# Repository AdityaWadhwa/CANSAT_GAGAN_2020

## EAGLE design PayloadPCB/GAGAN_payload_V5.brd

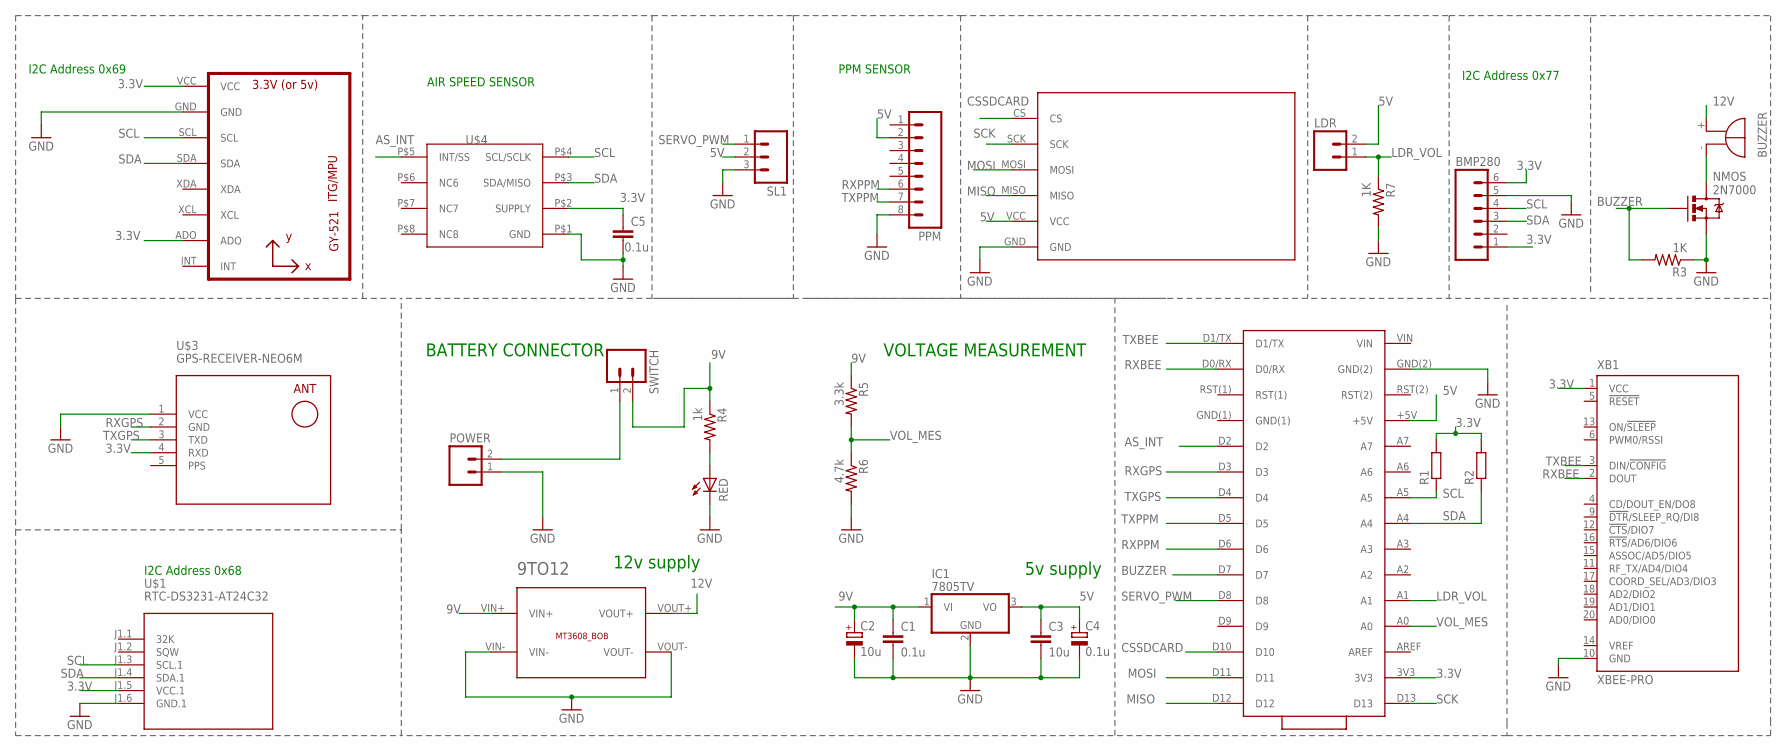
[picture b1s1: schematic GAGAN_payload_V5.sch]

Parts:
9TO12: BREAKOUTS_MT3608_BOB
BMP280: M06; 06P
C1, C5: 0.1u; C025-025X050
C2: 10u; E2,5-6
C3: 10u; C025-025X050
C4: 0.1u; E2,5-6
IC1: 7805TV; TO220V
LDR: M02; 02P
MOD1: ARDUINO(NANO_3.0); ARDUINO_NANO_30PIN
POWER: CEDT_JANUARY_2015_V5_M02; CEDT_JANUARY_2015_V5_02P
PPM: M08; 08P
Q1: SPARKFUN-DISCRETESEMI_MOSFET-NCHANNEL2N7000; SPARKFUN-DISCRETESEMI_TO-92
R1, R2: R-EU_0207/7; 0207/7
R3, R7: 1K; 0204/7
R4: 1k; 0204/7
R5: 3.3k; 0204/7
R6: 4.7k; 0204/7
RED: red; LED3MM
SG1: BUZZER_EB2209A
SL1: M03; 03P
SWITCH: M02; 02P
U1: GY-521MPU6050; GY-521
U$1: RTC-DS3231-AT24C32
U$3: GPS-RECEIVER-NEO6M
U$4: MS4525DO
U$5: SDCARD; M0SDCARDMODULE
XB1: XBEE-PRO

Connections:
3.3V: BMP280.1, BMP280.6, C5.1, MOD1.3V3, R1.2, R2.2, U1.ADO, U1.VCC, U$1.J1.5 (VCC.1), U$3.4 (RXD), U$4.P$2 (SUPPLY), XB1.1 (VCC)
5V: C3.1, C4.+, IC1.3 (VO), LDR.2, MOD1.+5V, PPM.2, SL1.2, U$5.VCC
9V: 9TO12.VIN+, C1.1, C2.+, IC1.1 (VI), R4.1, R5.1, SWITCH.2
12V: 9TO12.VOUT+, SG1.+
AS_INT: MOD1.D2, U$4.P$5 (INT/SS)
BUZZER: MOD1.D7, Q1.2 (G), R3.2
CSSDCARD: MOD1.D10, U$5.CS
GND: 9TO12.VIN-, 9TO12.VOUT-, BMP280.5, C1.2, C2.-, C3.2, C4.-, C5.2, IC1.2 (GND), MOD1.GND(2), POWER.1, PPM.8, Q1.1 (S), R3.1, R6.2, R7.2, RED.K (C), SL1.3, U1.GND, U$1.J1.6 (GND.1), U$3.1 (VCC), U$4.P$1 (GND), U$5.GND, XB1.10 (GND)
LDR_VOL: LDR.1, MOD1.A1, R7.1
MISO: MOD1.D12, U$5.MISO
MOSI: MOD1.D11, U$5.MOSI
unnamed: POWER.2, SWITCH.1
unnamed: R4.2, RED.A
unnamed: Q1.3 (D), SG1.-
PPS: U$3.5 (PPS)
RXBEE: MOD1.D0/RX, XB1.2 (DOUT)
RXGPS: MOD1.D3, U$3.2 (GND)
RXPPM: MOD1.D6, PPM.6
SCK: MOD1.D13, U$5.SCK
SCL: BMP280.4, MOD1.A5, R1.1, U1.SCL, U$1.J1.3 (SCL.1), U$4.P$4 (SCL/SCLK)
SDA: BMP280.3, MOD1.A4, R2.1, U1.SDA, U$1.J1.4 (SDA.1), U$4.P$3 (SDA/MISO)
SERVO_PWM: MOD1.D8, SL1.1
TXBEE: MOD1.D1/TX, XB1.3 (DIN/!CONFIG)
TXGPS: MOD1.D4, U$3.3 (TXD)
TXPPM: MOD1.D5, PPM.7
VOL_MES: MOD1.A0, R5.2, R6.1

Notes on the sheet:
BATTERY CONNECTOR
5v supply
I2C Address 0x77
I2C Address 0x68
I2C Address 0x69
AIR SPEED SENSOR
PPM SENSOR
VOLTAGE MEASUREMENT
12v supply

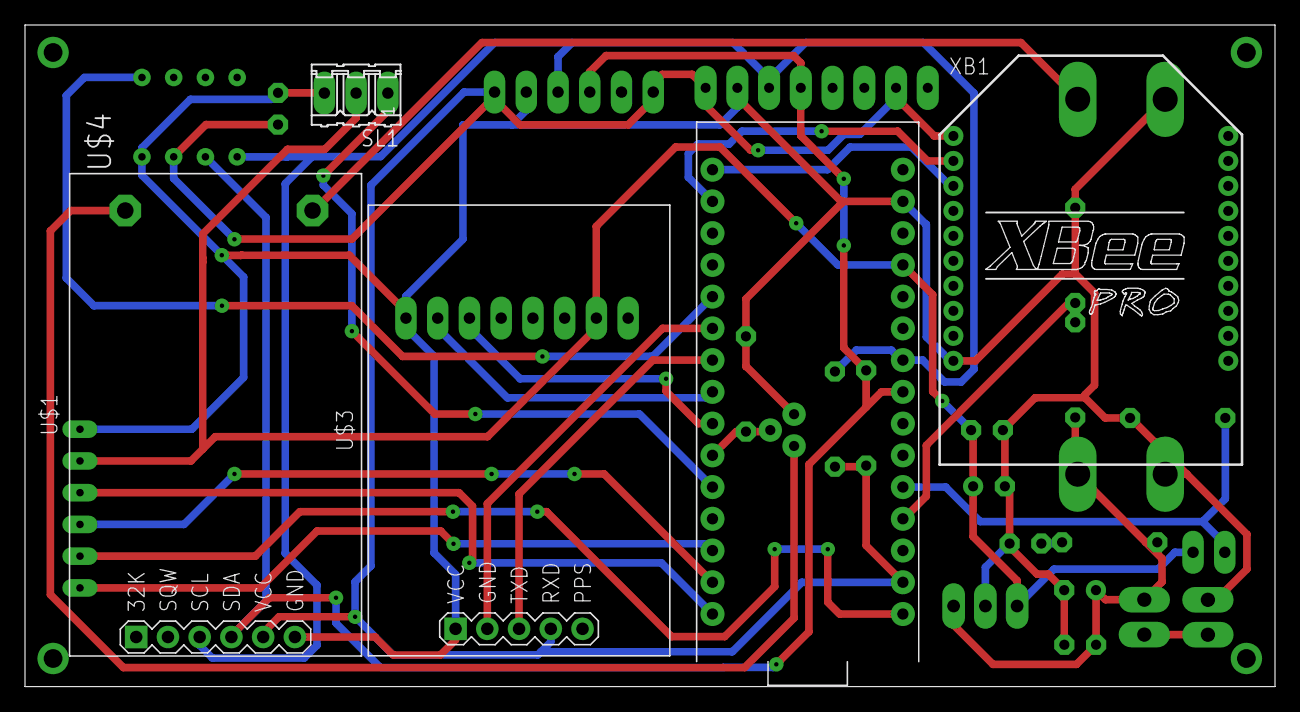
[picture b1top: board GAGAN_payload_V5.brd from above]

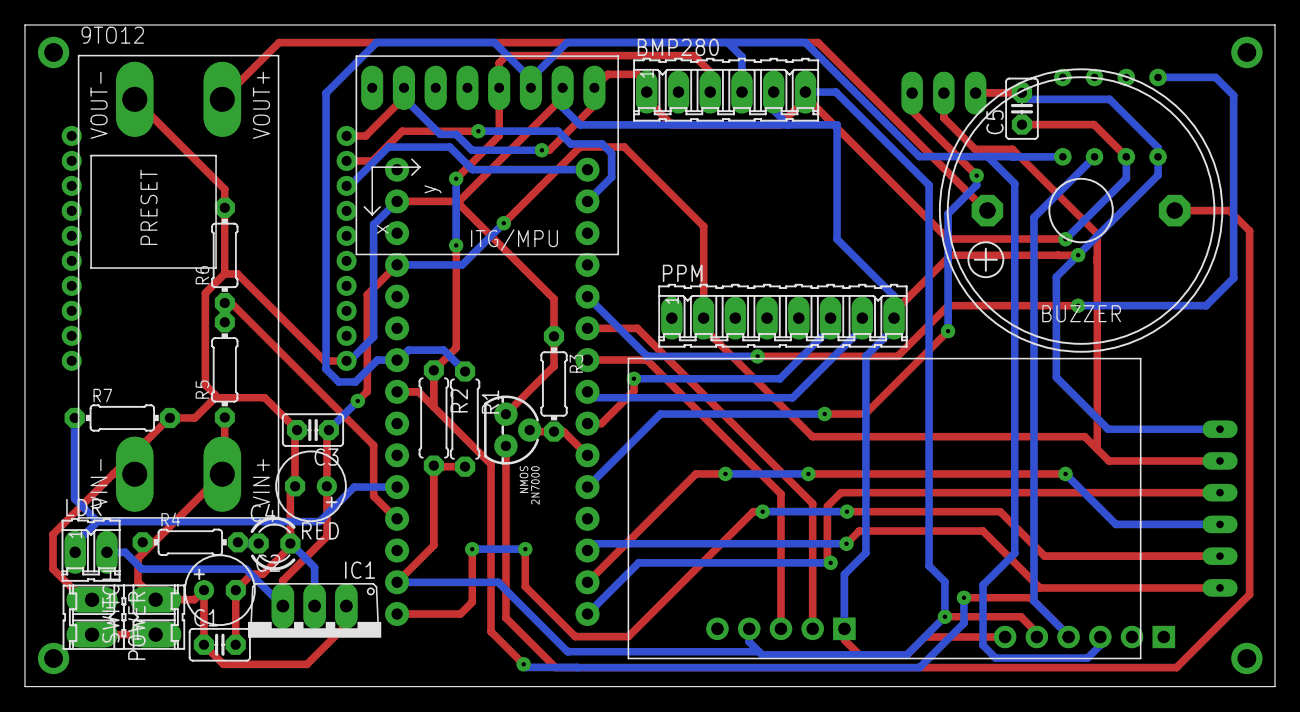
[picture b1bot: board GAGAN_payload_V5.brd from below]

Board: 2 copper layers, 100.0 x 53.0 mm, 30 parts (24 on the bottom side), 25 nets.

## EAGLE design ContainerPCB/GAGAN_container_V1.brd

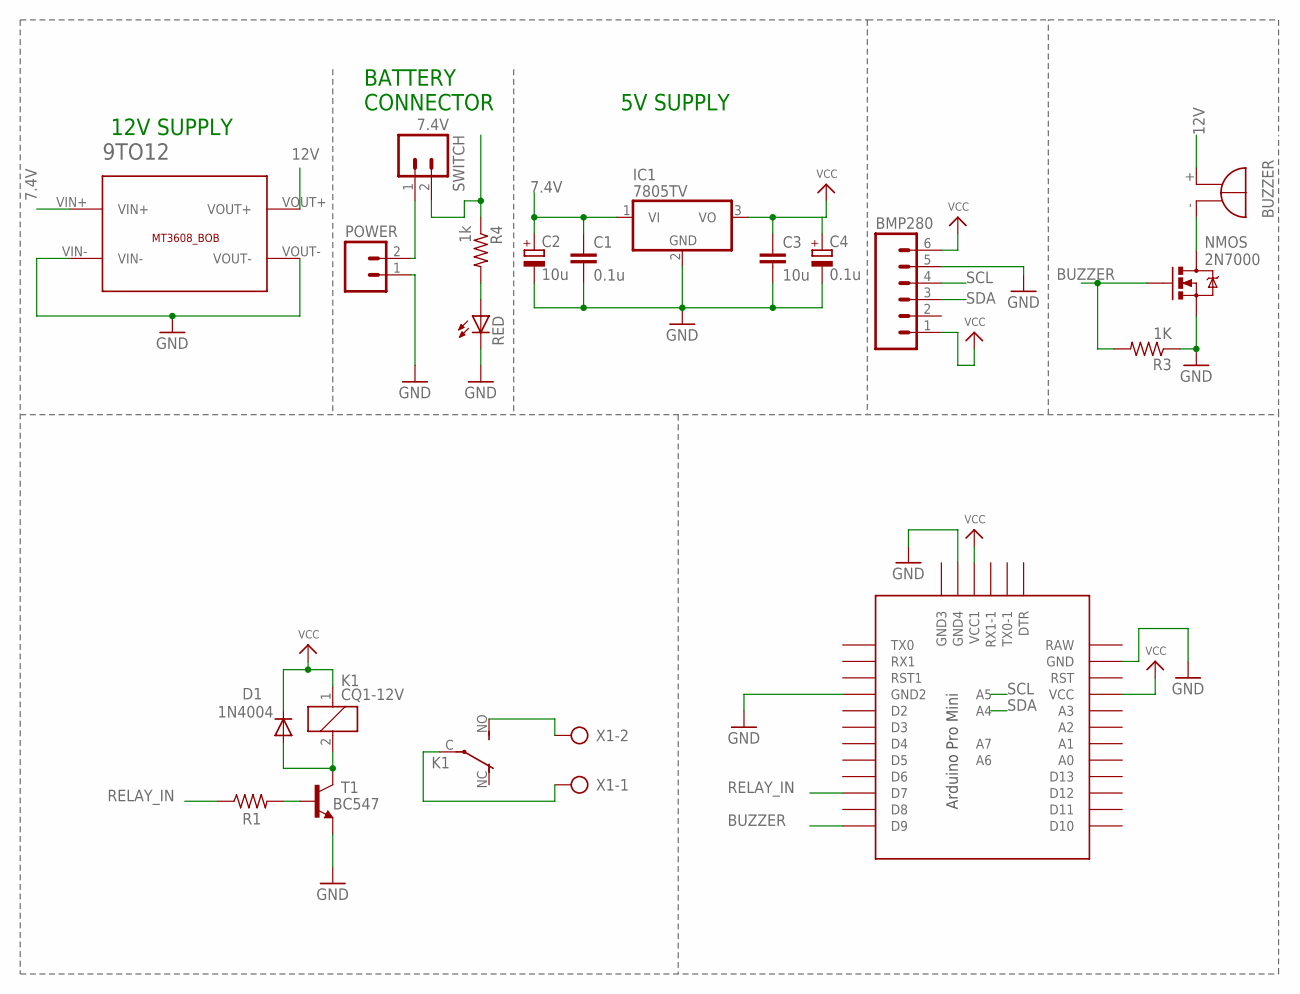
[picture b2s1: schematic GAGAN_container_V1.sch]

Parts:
9TO12: BREAKOUTS_MT3608_BOB
BMP280: M06; 06P
C1: 0.1u; C025-025X050
C2: 10u; E2,5-6
C3: 10u; C025-025X050
C4: 0.1u; E2,5-6
D1: 1N4004; DO41-10
IC1: 7805TV; TO220V
K1: CQ1-12V; CQ1
POWER: CEDT_JANUARY_2015_V5_M02; CEDT_JANUARY_2015_V5_02P
Q1: SPARKFUN-DISCRETESEMI_MOSFET-NCHANNEL2N7000; SPARKFUN-DISCRETESEMI_TO-92
R1: R-US_0207/7; 0207/7
R3: 1K; 0204/7
R4: 1k; 0204/7
RED: red; LED3MM
SG1: BUZZER_EB2209A
SWITCH: M02; 02P
T1: BC547; TO92
U$1: PRO-MINI-2
X1: AK500/2-H

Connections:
7.4V: 9TO12.VIN+, C1.1, C2.+, IC1.1 (VI), R4.1, SWITCH.2
12V: 9TO12.VOUT+, SG1.+
BUZZER: Q1.2 (G), R3.2, U$1.D9
GND: 9TO12.VIN-, 9TO12.VOUT-, BMP280.5, C1.2, C2.-, C3.2, C4.-, IC1.2 (GND), POWER.1, Q1.1 (S), R3.1, RED.K (C), T1.1 (E), U$1.GND, U$1.GND1 (GND2), U$1.GND3 (GND4)
unnamed: POWER.2, SWITCH.1
unnamed: R4.2, RED.A
unnamed: Q1.3 (D), SG1.-
unnamed: D1.A, K1.2, T1.3 (C)
unnamed: R1.2, T1.2 (B)
unnamed: K1.C, X1.1
unnamed: K1.NO (S), X1.2
RELAY_IN: R1.1, U$1.D7
SCL: BMP280.4, U$1.A5
SDA: BMP280.3, U$1.A4
VCC: BMP280.1, BMP280.6, C3.1, C4.+, D1.C, IC1.3 (VO), K1.1, U$1.VCC, U$1.VCC1

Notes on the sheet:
BATTERY CONNECTOR
5V SUPPLY
12V SUPPLY

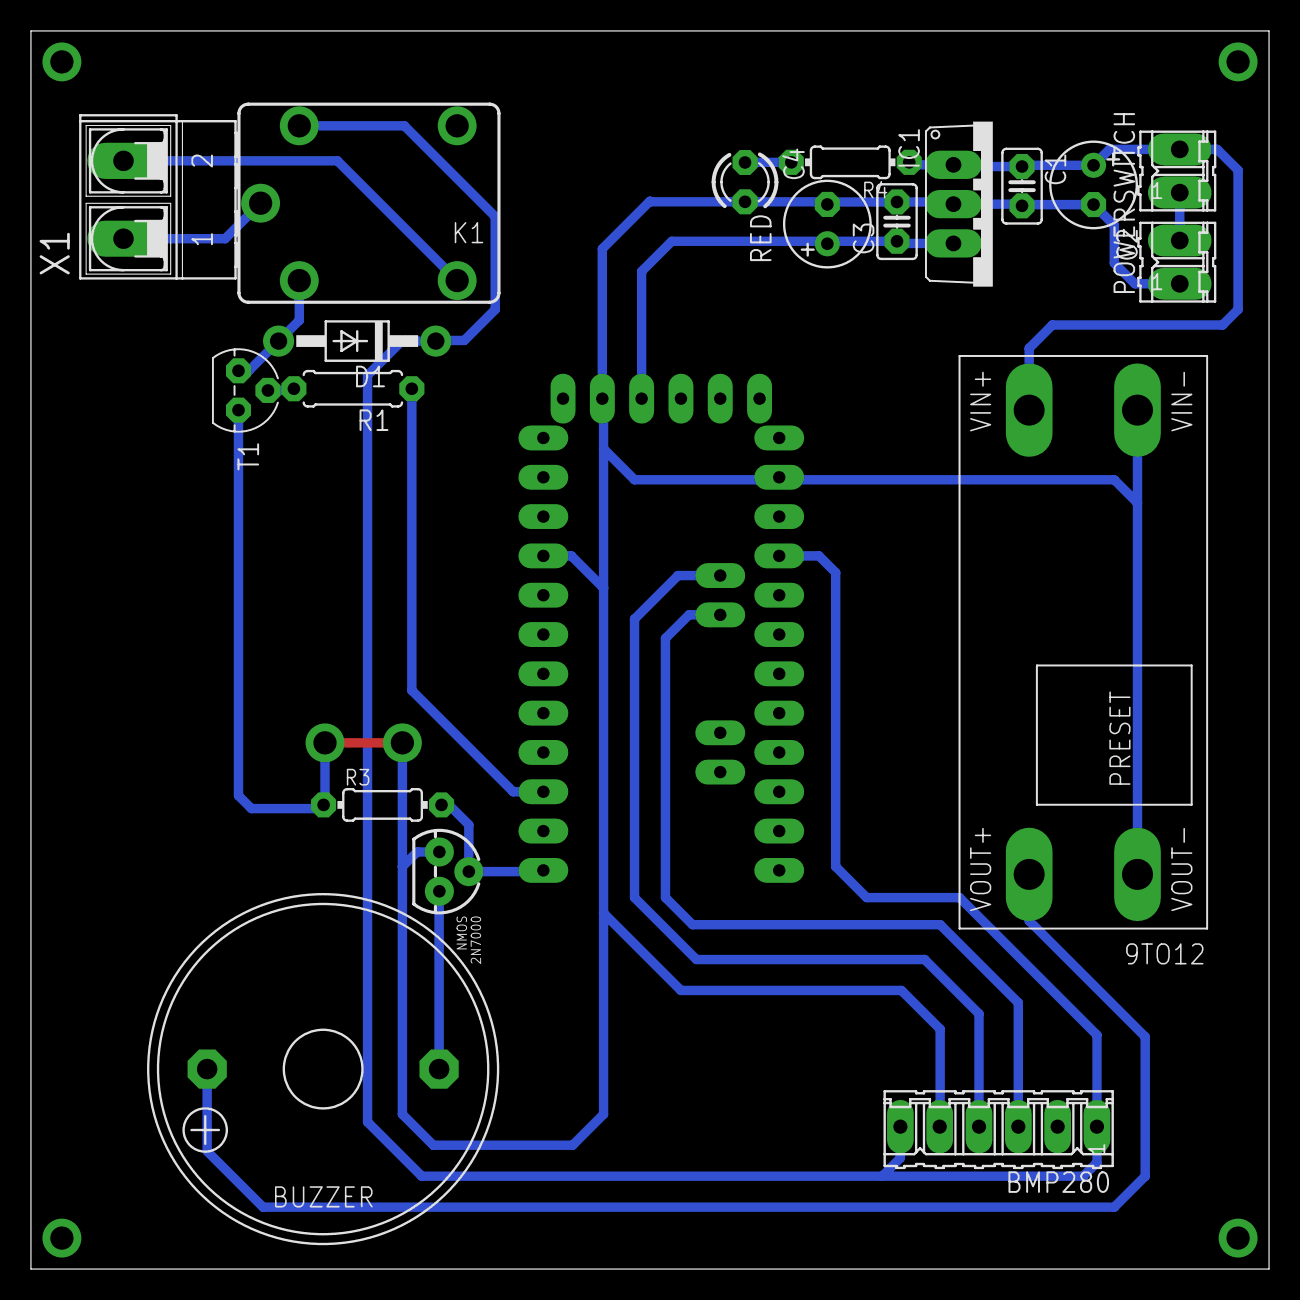
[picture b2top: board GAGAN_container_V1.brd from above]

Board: 2 copper layers, 80.0 x 80.0 mm, 20 parts (0 on the bottom side), 15 nets.

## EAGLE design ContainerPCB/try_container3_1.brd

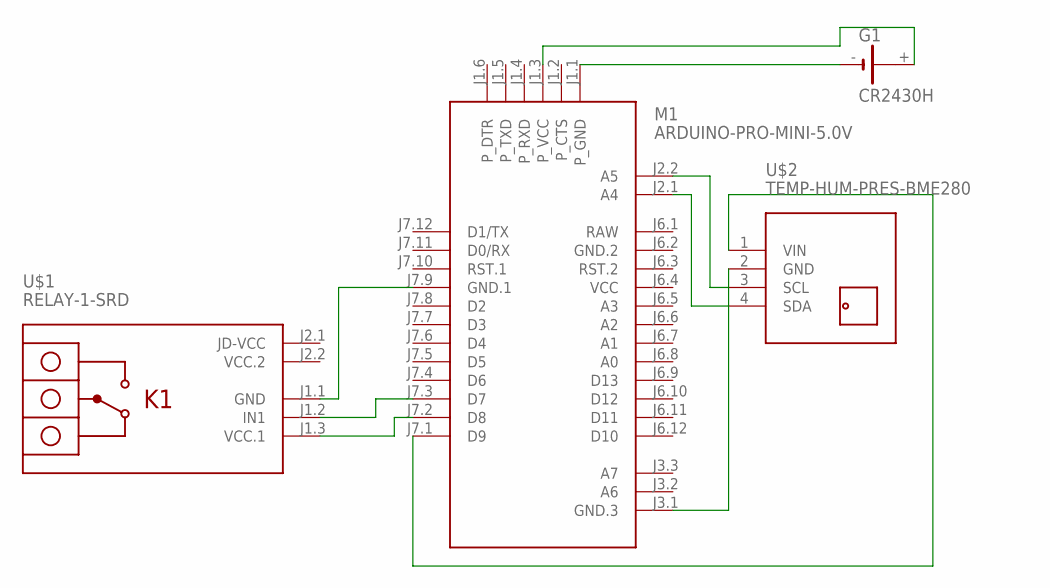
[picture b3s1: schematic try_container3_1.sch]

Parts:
G1: CR2430H
M1: ARDUINO-PRO-MINI-5.0V; ARDUINO-PRO-MINI
U$1: RELAY-1-SRD
U$2: TEMP-HUM-PRES-BME280

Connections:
GND.2: M1.J6.2 (GND.2)
unnamed: M1.J2.2 (A5), U$2.3 (SCL)
unnamed: M1.J2.1 (A4), U$2.4 (SDA)
unnamed: M1.J3.1 (GND.3), U$2.2 (GND)
unnamed: M1.J7.1 (D9), U$2.1 (VIN)
unnamed: M1.J7.3 (D7), U$1.J1.2 (IN1)
unnamed: M1.J7.2 (D8), U$1.J1.3 (VCC.1)
unnamed: M1.J7.9 (GND.1), U$1.J1.1 (GND)
unnamed: G1.+, M1.J1.3 (P_VCC)
unnamed: G1.-, M1.J1.1 (P_GND)
RAW: M1.J6.1 (RAW)
VCC: M1.J6.4 (VCC)
VCC.2: U$1.J2.2 (VCC.2)

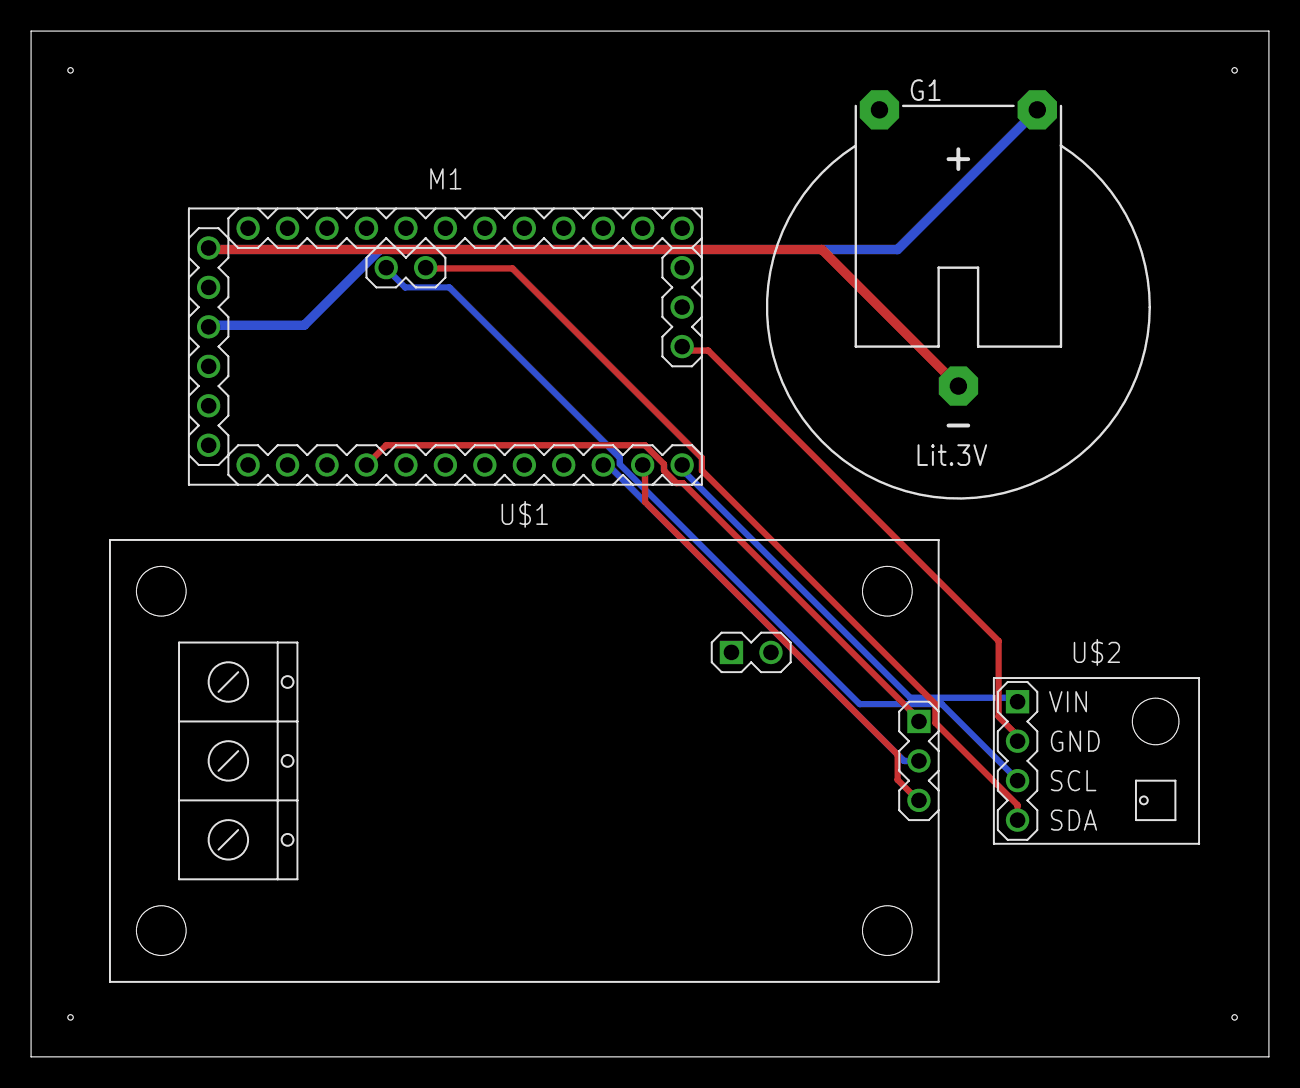
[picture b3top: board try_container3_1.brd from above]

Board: 2 copper layers, 79.7 x 66.0 mm, 4 parts (0 on the bottom side), 9 nets.

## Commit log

2019-11-09 Initial
2019-11-09 Payload PCB initial design
2019-11-10 Container PCB Initial
2019-11-11 Payload PCB SolidWorks modifications
2019-11-21 Servo Added
2019-12-19 upto SD Card
2019-12-26 Payload PCB fixed holes in some parts
2020-01-20 PCB test code
2020-03-15 Libraries Added, integrated code, currently too big
2020-03-16 XBEE Transmitting
2020-03-21 Nano Code fits(barely). Code for Teensy also added

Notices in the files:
parts and their libraries:
diy-modules: Released under the Creative Commons Attribution 4.0 International License: http://creativecommons.org/licenses/by/4.0
